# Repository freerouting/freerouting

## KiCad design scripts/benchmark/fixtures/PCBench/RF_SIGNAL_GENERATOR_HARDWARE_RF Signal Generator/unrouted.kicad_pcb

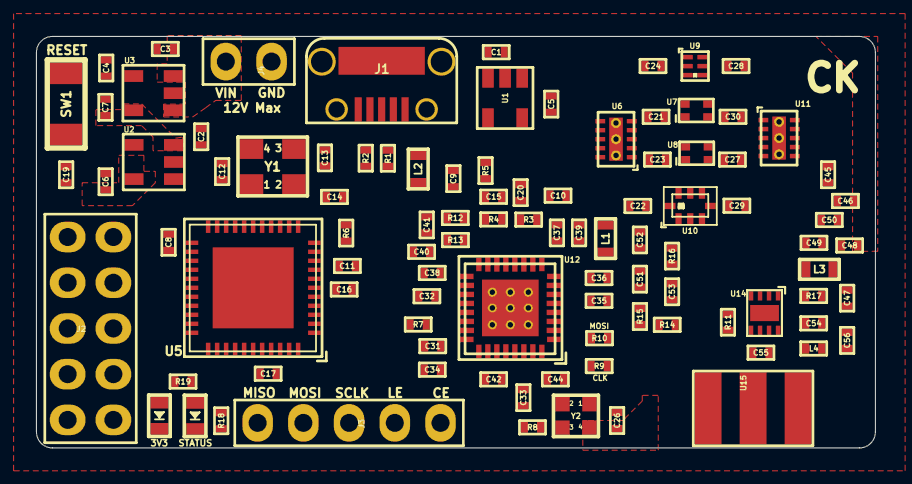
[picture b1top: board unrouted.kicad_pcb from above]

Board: 4 copper layers, 46.6 x 22.9 mm, 98 parts (0 on the bottom side), 80 nets, no tracks yet.

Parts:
3V3: Led_Diode; Diode_0603
C1, C2, C3, C4, C5, C6, C7: 2.2uF; SMD_0402
C8, C14, C17, C19, C35, C36, C38, C40, C42, C44, C48, C50, C51: 100nF; SMD_0402
C9, C10, C37, C39, C41: 100pF; SMD_0402
C11, C16, C31, C32, C34: 1uF; SMD_0402
C12, C13: 15pF; SMD_0402
C15, C20, C45, C55: 1nF; SMD_0402
C21, C22, C23, C24, C27, C28, C29, C30, C54: 10pF; SMD_0402
C26, C33, C56: 10nF; SMD_0402
C46, C47: DNP; SMD_0402
C49: 10uF; SMD_0402
C52: 12nF; SMD_0402
C53: 820pF; SMD_0402
J1: USB_MicroB; USB_MicroB_TH
J2: Connector_02x05; PinHeader_2x5_P2.54mm
J3: Connector_01x05; PinHeader_1x5_P2.54mm
J4: Connector_01x02; PinHeader_1x2_P2.54mm
L1, L2, L3: BLM18PG181SN1D; SMD_0603
L4: LQW15AN9N9J80D; SMD_0402
R1, R2: 22; SMD_0402
R3, R4, R5: 49.9; SMD_0402
R6: 10K; SMD_0402
R7: 5.11K; SMD_0402
R8, R9, R10, R12, R13: 0; SMD_0402
R11: 100; SMD_0402
R14: 90.9; SMD_0402
R15: 30.1; SMD_0402
R16: 240; SMD_0402
R17: 1.8; SMD_0402
R18, R19: 1K; SMD_0402
STATUS: Led_Diode; Diode_0603
SW1: RESET_BUTTON; Button_B3U_1000P
U1, U2: LP5907; SOT23_5
U3: MIC5219; SOT23_5
U5: ATMEGA32U4; QFN44_7x7mm_P0.5mm_1EXP_4.5x4.5mm
U6, U11: SKY13322_375LF; MLPD_10
U7: LPF_LP0603A0902ANTR
U8: LPF_LP0603A1842ANTR
U9: LPF_3550LP14A300T
U10: LPF_5515LP15A730E
U12: MAX2871; QFN32_5x5mm_P0.5mm_1EXP_3.1x3.1mm
U14: TRF37A75; WSON8_2x2mm_P0.5mm_1EXP_0.9x1.6mm
U15: SMA_Connector
Y1: 8MHz; Crystal_3.2x2.5mm
Y2: ASTX-13-D-19.200MHz-I05-T; Crystal_2x1.6mm

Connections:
+3V3: 3V3.2, C6.1, C8.1, C14.1, C26.1, C42.2, C44.2, R6.1, R11.1, U2.5, U5.14, U5.24, U5.34, U5.44, U12.28, U12.32, Y2.4
+5V: C1.1, C2.1, C7.1, C11.1, C46.1, C47.1, C48.1, J1.1, L3.1, U1.1, U1.3, U2.1, U2.3, U3.5, U5.2, U5.7
+VBattery: C3.1, J4.2, U3.1, U3.3
/3.3V_RF: C5.1, C9.2, C10.2, L1.1, L2.1, R3.1, R4.1, R12.1, R13.1, U1.5
/D+: R2.2, U5.4
/D-: R1.2, U5.3
/RST: C19.2, R6.2, SW1.1, U5.13
ADC6: J2.10, U5.37
ADC7: J2.9, U5.36
AMP_PWDN: J2.6, R11.2, U5.30, U14.5
GND: C1.2, C2.2, C3.2, C4.2, C5.2, C6.2, C7.2, C8.2, C9.1, C10.1, C11.2, C12.2, C13.2, C14.2, C16.2, C17.2, C19.1, C26.2, C31.1, C32.1, C34.1, C35.1, C36.1, C37.1, C38.1, C39.1, C40.1, C41.1, C42.1, C44.1, C46.2, C47.2, C48.2, C49.2, C50.2, C52.1, C53.1, C54.2, C56.2, J1.5, J4.1, R5.1, R7.2, R14.1, R18.2, R19.2, SW1.2, U1.2, U2.2, U3.2, U5.5, U5.15, U5.23, U5.33, U5.35, U5.43, U5.45, U6.11, U7.3, U7.4, U8.3, U8.4, U9.1, U9.3, U9.4, U9.6, U10.1, U10.3, U10.5, U10.7, U11.11, U12.8, U12.9, U12.11, U12.18, U12.21, U12.27, U12.31, U12.33, U14.3, U14.4, U14.6, U14.8, U14.9, U15.2, U15.3, U15.4, U15.5, Y1.2, Y1.4, Y2.1, Y2.2
MAX2871_CE: J3.1, U5.8, U12.4
MAX2871_LD: J2.7, U5.31, U12.25
MAX2871_LE: J3.2, U5.1, U12.3
MAX2871_MUX: J2.8, U5.32, U12.30
unnamed: C4.1, U3.4
unnamed: C12.1, U5.17, Y1.1
unnamed: C13.1, U5.16, Y1.3
unnamed: C15.2, R5.2
unnamed: C16.1, U5.6
unnamed: C17.1, U5.42
unnamed: C20.2, U6.8
unnamed: C21.1, U7.1
unnamed: C21.2, U6.5
unnamed: C22.1, U10.8
unnamed: C22.2, U6.10
unnamed: C23.1, U8.1
unnamed: C23.2, U6.1
unnamed: C24.1, U9.2
unnamed: C24.2, U6.6
unnamed: C27.1, U11.5
unnamed: C27.2, U8.2
unnamed: C28.1, U11.10
unnamed: C28.2, U9.5
unnamed: C29.1, U11.6
unnamed: C29.2, U10.4
unnamed: C30.1, U11.1
unnamed: C30.2, U7.2
unnamed: C31.2, U12.23
unnamed: C32.2, U12.19
unnamed: C33.1, U12.29
unnamed: C33.2, R8.2
unnamed: C34.2, U12.24
unnamed: C35.2, C36.2, C37.2, C39.2, L1.2, U12.6, U12.10
unnamed: C38.2, C40.2, C41.2, L2.2, U12.16, U12.17
unnamed: C45.1, U14.2
unnamed: C45.2, U11.8
unnamed: C49.1, C50.1, L3.2, R17.1, U14.1
unnamed: C51.1, C52.2, R16.1, U12.7
unnamed: C51.2, R15.1
unnamed: C53.2, R16.2, U12.20
unnamed: C54.1, C56.1, L4.1, R17.2
unnamed: C55.1, L4.2, U14.7
unnamed: C55.2, U15.1
unnamed: R18.1, STATUS.1
unnamed: 3V3.1, R19.1
unnamed: J1.2, R1.1
unnamed: J1.3, R2.1
unnamed: R7.1, U12.22
unnamed: R9.2, U12.1
unnamed: R10.2, U12.2
unnamed: R12.2, U12.14
unnamed: R13.2, U12.15
unnamed: R14.2, R15.2, U12.5
REF_IN: R8.1, Y2.3
RFOUTA_N: C15.1, R4.2, U12.13
RFOUTA_P: C20.1, R3.2, U12.12
RFOUT_EN: J2.5, U5.29, U12.26
RX: J2.3, U5.20
SCL: J2.1, U5.18
SDA: J2.2, U5.19
SPI_CLK: J3.3, R9.1, U5.9
SPI_MISO: J3.5, U5.11
SPI_MOSI: J3.4, R10.1, U5.10
STATUS_LED: STATUS.2, U5.38
SWITCH_V1: U5.25, U6.9, U11.7
SWITCH_V2: U5.26, U6.7, U11.9
SWITCH_V3: U5.27, U6.2, U11.4
SWITCH_V4: U5.28, U6.4, U11.2
TX: J2.4, U5.21

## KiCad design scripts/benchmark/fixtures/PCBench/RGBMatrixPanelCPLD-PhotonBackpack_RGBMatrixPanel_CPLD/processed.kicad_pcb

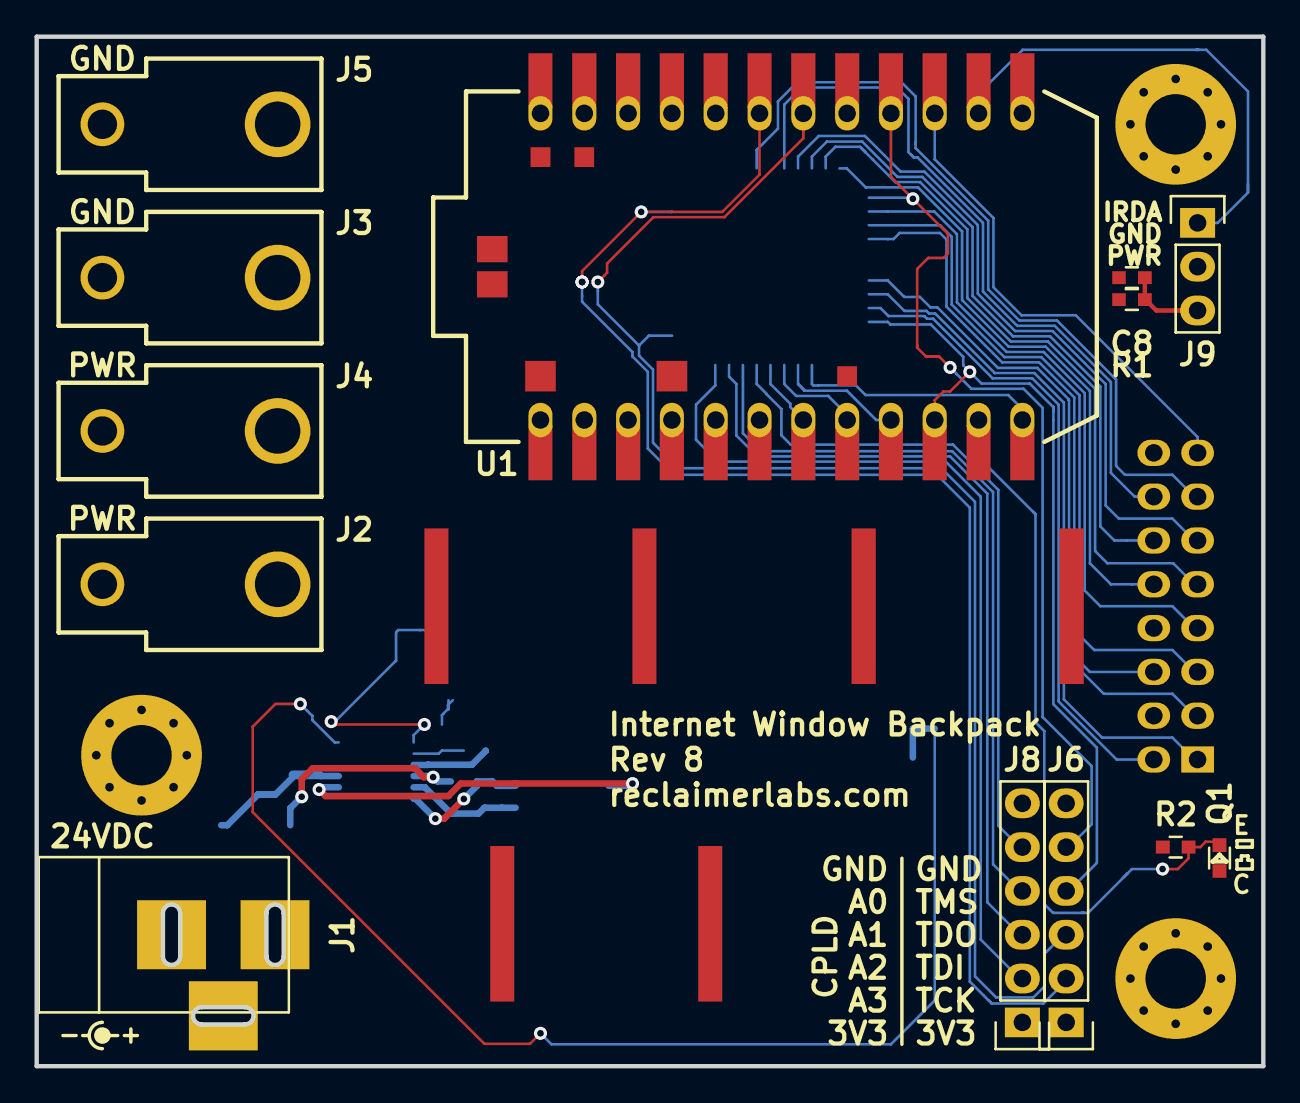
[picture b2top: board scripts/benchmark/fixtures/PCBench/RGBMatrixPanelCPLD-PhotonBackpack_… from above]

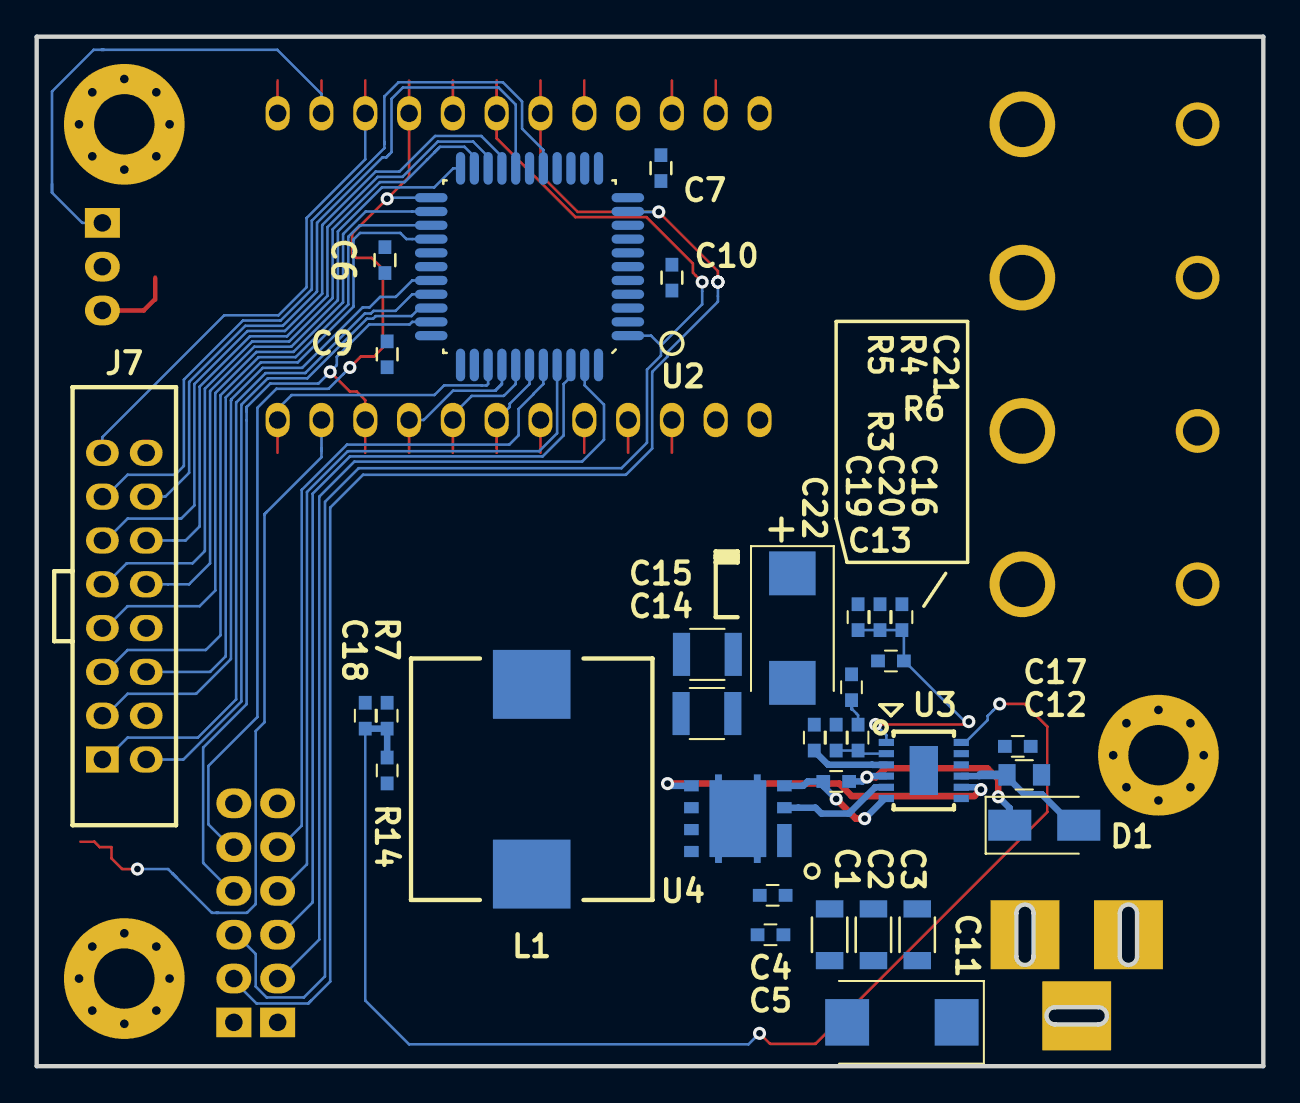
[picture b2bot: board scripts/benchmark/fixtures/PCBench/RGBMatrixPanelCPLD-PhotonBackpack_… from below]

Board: 2 copper layers, 71.1 x 59.7 mm, 52 parts (33 on the bottom side), 43 nets.

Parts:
C1, C2, C3: 10uF; C_1206
C4, C6, C7, C8, C9, C10, C18, C19: 0.1uF; C_0603
C5, C13, C17: 1uF; C_0603
C11: DNP; CP_Tantalum_Case-D_EIA-7343-31_Reflow
C12: 10uF; C_0805
C14, C15: 100uF; C_1210
C16: 2200pF; C_0603
C20: 100pF; C_0603
C21: DNP; C_0603
C22: 100uF; CP_Tantalum_Case-D_EIA-7343-31_Reflow
D1: B140; D_SMA_Standard
J1: BARREL_JACK; BARREL_JACK_PJ_202AH_Slots
J2, J3, J4, J5: CONN_01X01; 3547
J6, J8: CONN_01X06; Socket_Strip_Straight_1x06
J7: CONN_02X08; HEADER_THRU_02x08_POL
J9: CONN_01X03; Socket_Strip_Straight_1x03
L1: 1.5uH; SRR1270
Q1: Photo_Trans; Photo_Trans_ALS-PT19-315C
R1: 100R; C_0603
R2, R3, R6: 10k; C_0603
R4, R5: 100k; C_0603
R7: 28k0; C_0603
R14: 7k32; C_0603
U1: PHOTON
U2: LC4032V-44TQFP; QFP_44
U3: LTC3854; 12-MSE
U4: CSD87351Q5D
X1, X2, X3: MTHOLE; MountingHole_3.5mm_Pad_Via
X4, X5, X6: HEATSiNK; 573100D00010G

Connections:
+3V3: C6.1, C7.1, C9.1, C10.1, J6.1, J8.1, Q1.C, R1.1, U1.24, U2.6, U2.11, U2.28, U2.33
+5V: C14.1, C15.1, C18.1, C21.2, C22.1, J2.1, J4.1, L1.2, R4.2, R5.2, R7.2, U1.1, U3.11
/A: J7.9, U2.21
/B: J7.10, U2.22
/B1: J7.3, U2.29
/B2: J7.7, U2.24
/C: J7.11, U2.19
/CLK: J7.13, U2.16
/CPLD_A0: J8.5, U2.40
/CPLD_A1: J8.4, U2.41
/CPLD_A2: J8.3, U2.42
/CPLD_A3: J8.2, U2.43
/D: J7.12, U2.20
/DRVH: U3.5, U4.3
/DRVL: U3.8, U4.5
/FB: C21.1, R4.1, R5.1, R6.2, U3.1
/G1: J7.2, U2.31
/G2: J7.6, U2.26
/INTVCC: C12.1, D1.2, U3.9
/IRDA: J9.1, U1.14
/IR_PWR: C8.1, J9.3, R1.2
/ITH: C16.1, C20.1, U3.2
/LAT: J7.14, U2.18
/OE: J7.15, U1.15
/PHOTO: Q1.E, R2.1, U1.11
/R1: J7.1, U2.30
/R2: J7.5, U2.25
/RST_CPLD: U1.12, U2.36
/SENSE+: C18.2, R7.1, R14.1, U3.12
/SPI_MISO: U1.8, U2.38
/SPI_MOSI: U1.7, U2.39
/SPI_SCK: U1.9, U2.37
/SS: C19.1, U3.3
/SW: C13.1, U3.6, U4.4
/TCK: J6.2, U1.19, U2.10
/TDI: J6.3, U1.18, U2.1
/TDO: J6.4, U1.10, U2.32
/TMS: J6.5, U1.16, U2.23
GND: C1.2, C2.2, C3.2, C4.2, C5.2, C6.2, C7.2, C8.2, C9.2, C10.2, C11.2, C12.2, C14.2, C15.2, C17.2, C19.2, C20.2, C22.2, J1.2, J3.1, J5.1, J6.6, J7.4, J7.8, J7.16, J8.6, J9.2, R2.2, R3.2, R6.1, U1.2, U1.21, U2.5, U2.12, U2.27, U2.34, U3.7, U3.13, U4.9, X1.1, X2.1, X3.1, X4.1, X5.1, X6.1
unnamed: C13.2, D1.1, U3.4
unnamed: C16.2, R3.1
unnamed: L1.1, R14.2, U4.6, U4.7, U4.8
VIN: C1.1, C2.1, C3.1, C4.1, C5.1, C11.1, C17.1, J1.1, U3.10, U4.1

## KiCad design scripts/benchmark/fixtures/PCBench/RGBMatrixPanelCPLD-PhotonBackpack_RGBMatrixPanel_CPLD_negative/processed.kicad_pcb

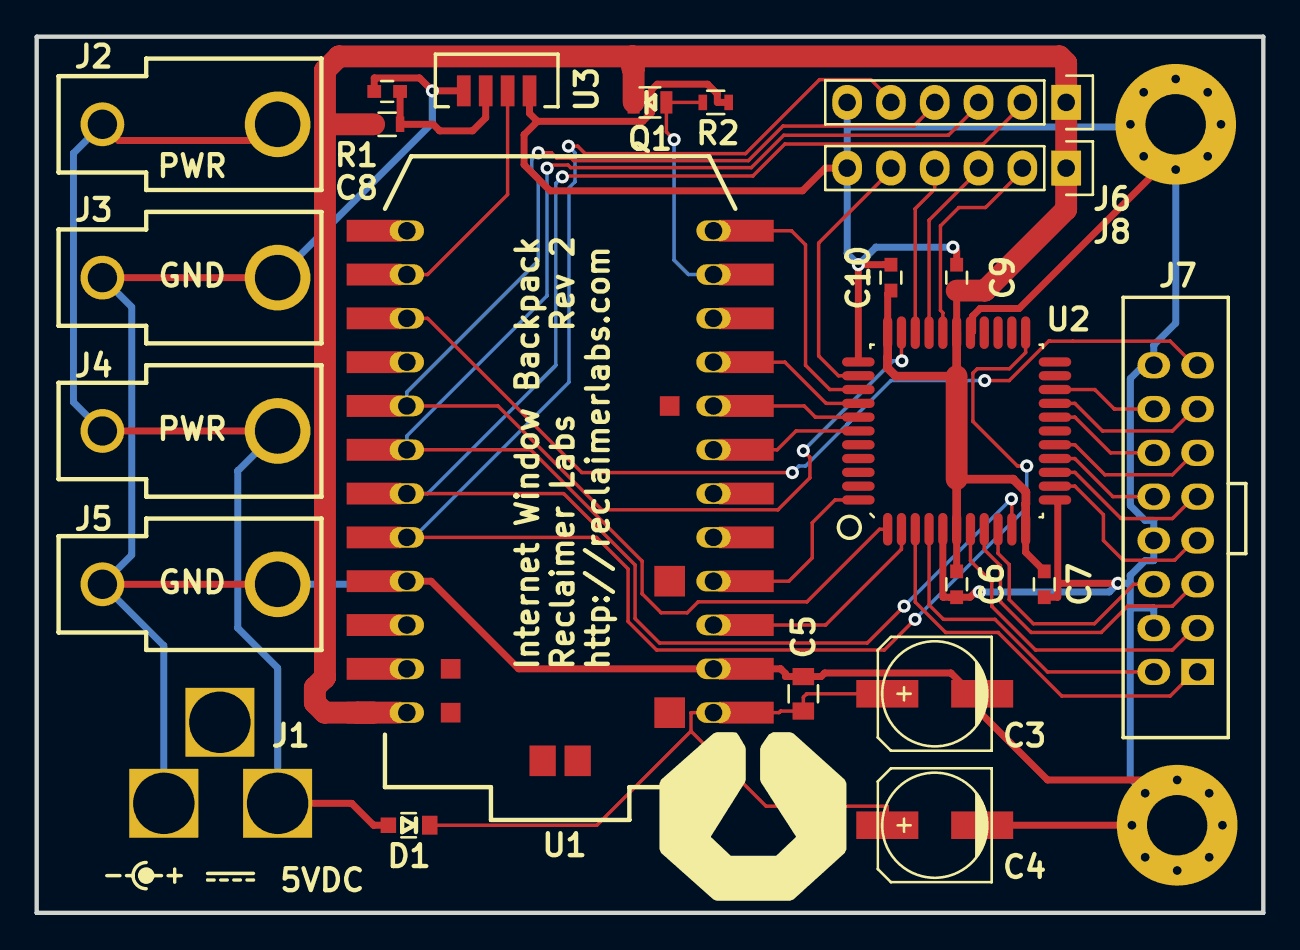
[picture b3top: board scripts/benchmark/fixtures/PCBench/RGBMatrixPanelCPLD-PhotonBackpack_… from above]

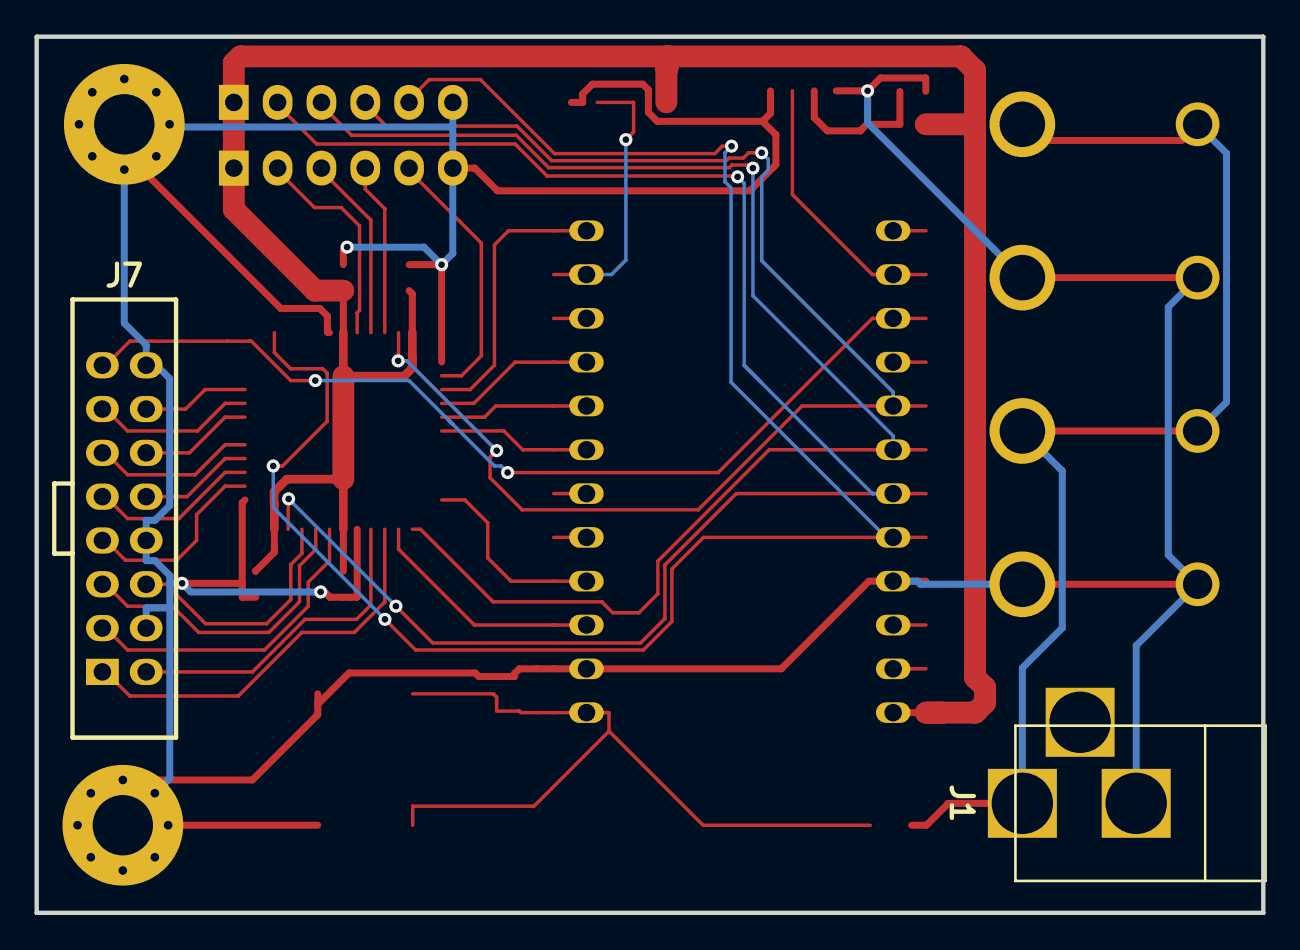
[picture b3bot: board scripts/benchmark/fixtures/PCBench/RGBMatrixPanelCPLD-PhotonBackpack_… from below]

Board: 2 copper layers, 71.1 x 50.8 mm, 25 parts (2 on the bottom side), 34 nets.

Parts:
C3, C4: 100uF; c_elec_6.3x5.7
C5: 10uF; C_0805
C6, C7, C8, C9, C10: 0.1uF; C_0603
D1: D_Schottky; SMini2-F5-B
J1: BARREL_JACK; BARREL_JACK_MPD_EJ508A
J2, J3, J4, J5: CONN_01X01; 3547
J6, J8: CONN_01X06; Socket_Strip_Straight_1x06
J7: CONN_02X08; HEADER_THRU_02x08_POL
Q1: Photo_Trans; Photo_Trans_0805
R1: 100R; R_0603
R2: 10k; R_0603
U1: PHOTON
U2: LC4032V-44TQFP; QFP_44
U3: TSOP75238TT
X3, X4: MTHOLE; MountingHole_3.5mm_Pad_Via

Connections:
+3V3: C6.1, C7.1, C9.1, C10.1, J6.1, J8.1, Q1.C, R1.1, U1.24, U2.6, U2.11, U2.28, U2.33
+5V: D1.2, J1.1, J2.1, J4.1
+5VA: C3.1, C4.1, C5.1, D1.1, U1.1
/A: J7.9, U2.14
/B: J7.10, U2.15
/B1: J7.3, U2.7
/B2: J7.7, U2.13
/C: J7.11, U2.16
/CLK: J7.13, U2.19
/CPLD_B8: J8.2, U2.29
/CPLD_B9: J8.3, U2.30
/CPLD_B10: J8.4, U2.31
/CPLD_B12: J8.5, U2.35
/D: J7.12, U2.18
/G1: J7.2, U2.4
/G2: J7.6, U2.9
/IRDA: U1.14, U3.3
/LAT: J7.14, U2.20
/OE: J7.15, U1.15
/PHOTO: Q1.E, R2.1, U1.11
/R1: J7.1, U2.3
/R2: J7.5, U2.8
/RST_CPLD: U1.12, U2.36
/SPI_MISO: U1.8, U2.38
/SPI_MOSI: U1.7, U2.39
/SPI_SCK: U1.9, U2.37
/TCK: J6.2, U1.19, U2.10
/TDI: J6.3, U1.18, U2.1
/TDO: J6.4, U1.17, U2.32
/TMS: J6.5, U1.20, U2.23
/UART_RX: U1.4, U2.44
/UART_TX: U1.3, U2.2
GND: C3.2, C4.2, C5.2, C6.2, C7.2, C8.2, C9.2, C10.2, J1.2, J3.1, J5.1, J6.6, J7.4, J7.8, J7.16, J8.6, R2.2, U1.2, U1.21, U2.5, U2.12, U2.27, U2.34, U3.1, U3.4, X3.1, X4.1
unnamed: C8.1, R1.2, U3.2
